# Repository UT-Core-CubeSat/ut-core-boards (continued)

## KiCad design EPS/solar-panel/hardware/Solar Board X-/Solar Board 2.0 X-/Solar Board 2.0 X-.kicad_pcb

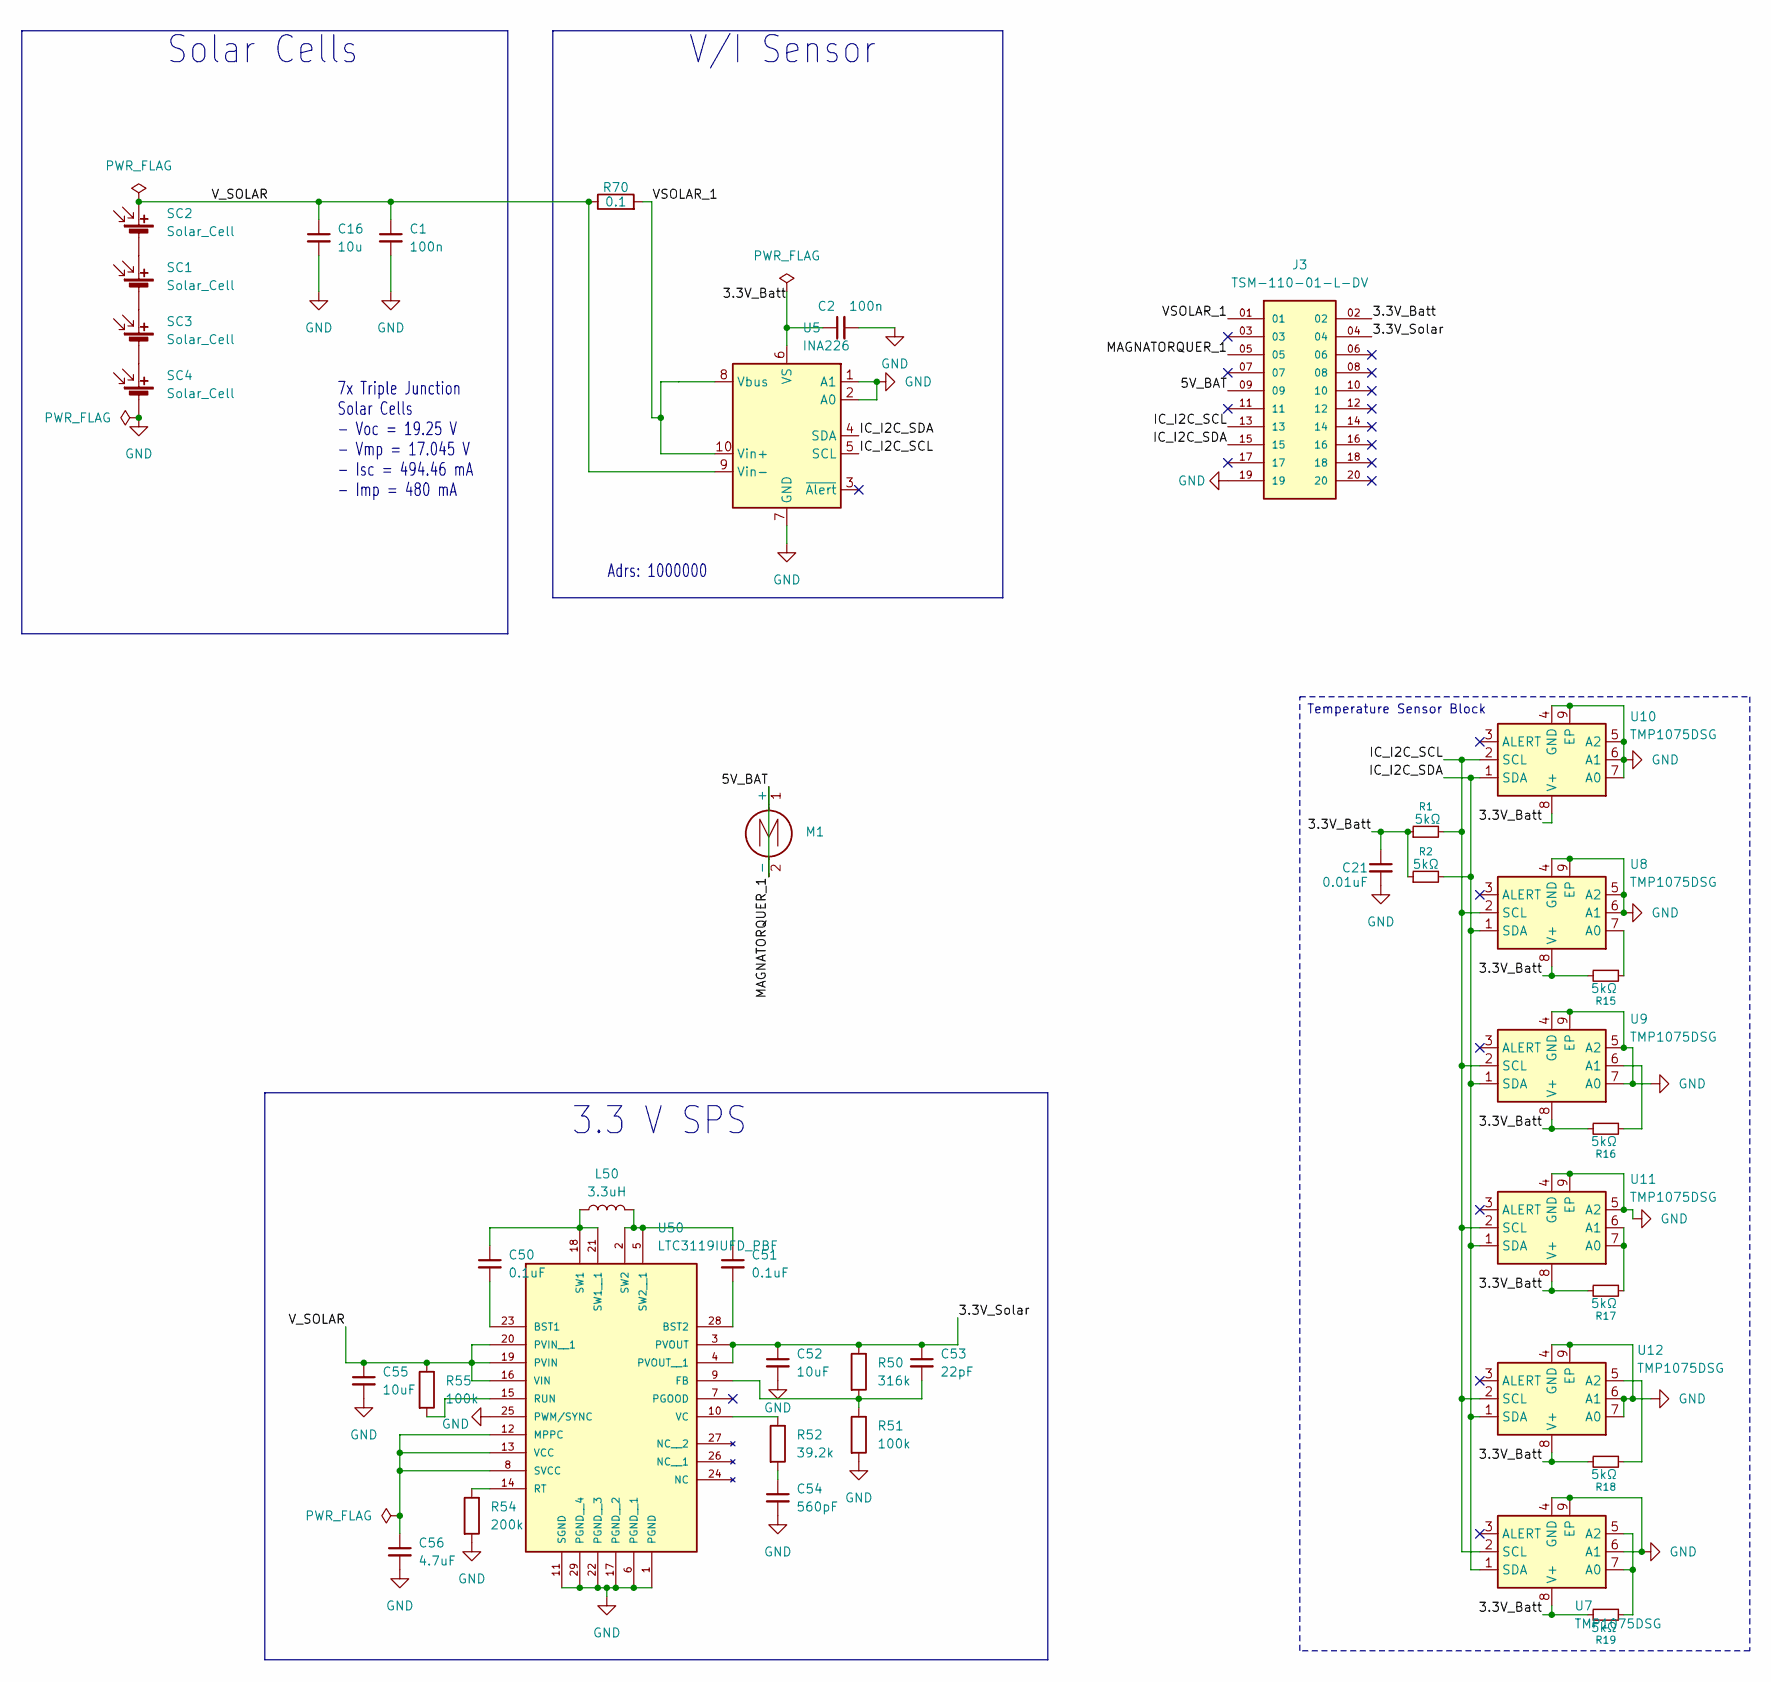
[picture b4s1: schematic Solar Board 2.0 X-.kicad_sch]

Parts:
C1, C2: 100n; C_0603_1608Metric
C16: 10u; C_0603_1608Metric
C21: 0.01uF; C_0402_1005Metric
C50, C51: 0.1uF; C_0201_0603Metric
C52: 10uF; C_0201_0603Metric
C53: 22pF; C_0201_0603Metric
C54: 560pF; C_0201_0603Metric
C55: 10uF; C_0603_1608Metric
C56: 4.7uF; C_0805_2012Metric
J3: TSM-110-01-L-DV; 2x10 Pin Header
L50: 3.3uH; L_0603_1608Metric
M1: Motor_DC; PinHeader_1x02_P2.54mm_Vertical
R1, R2, R15, R16, R17, R18, R19: 5kΩ; R_0201_0603Metric
R50: 316k; R_0201_0603Metric
R51, R55: 100k; R_0201_0603Metric
R52: 39.2k; R_0201_0603Metric
R54: 200k; R_0201_0603Metric
R70: 0.1; R_2512_6332Metric
SC1, SC2, SC3, SC4: Solar_Cell
U5: INA226; VSSOP-10_3x3mm_P0.5mm
U7, U8, U9, U10, U11, U12: TMP1075DSG; WSON-8-1EP_2x2mm_P0.5mm_EP0.9x1.6mm
U50: LTC3119IUFD_PBF; LTC3119

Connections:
/3.3V_Batt: C2.1, C21.1, J3.02, R1.1, R2.1, R15.2, R16.2, R17.2, R18.2, R19.2, U5.6 (VS), U7.8 (V+), U8.8 (V+), U9.8 (V+), U10.8 (V+), U11.8 (V+), U12.8 (V+)
/3.3V_Solar: C52.1, C53.1, J3.04, R50.1, U50.3 (PVOUT), U50.4 (PVOUT__1)
/5V_BAT: J3.05, J3.09, M1.1 (+), M1.2 (-)
/IC_I2C_SCL: J3.13, R1.2, U5.5 (SCL), U7.2 (SCL), U8.2 (SCL), U9.2 (SCL), U10.2 (SCL), U11.2 (SCL), U12.2 (SCL)
/IC_I2C_SDA: J3.15, R2.2, U5.4 (SDA), U7.1 (SDA), U8.1 (SDA), U9.1 (SDA), U10.1 (SDA), U11.1 (SDA), U12.1 (SDA)
/VSOLAR_1: J3.01, R70.2, U5.8 (Vbus), U5.10 (Vin+)
/V_SOLAR: C1.1, C16.1, C55.1, R55.1, R70.1, SC2.1 (+), U5.9 (Vin-), U50.16 (VIN), U50.19 (PVIN), U50.20 (PVIN__1)
GND: C1.2, C2.2, C16.2, C21.2, C52.2, C54.2, C55.2, C56.2, J3.19, R51.2, R54.2, SC4.2 (-), U5.1 (A1), U5.2 (A0), U5.7 (GND), U7.4 (GND), U7.6 (A1), U7.9 (EP), U8.4 (GND), U8.5 (A2), U8.6 (A1), U8.9 (EP), U9.4 (GND), U9.5 (A2), U9.7 (A0), U9.9 (EP), U10.4 (GND), U10.5 (A2), U10.6 (A1), U10.7 (A0), U10.9 (EP), U11.4 (GND), U11.5 (A2), U11.9 (EP), U12.4 (GND), U12.6 (A1), U12.7 (A0), U12.9 (EP), U50.1 (PGND), U50.6 (PGND__1), U50.11 (SGND), U50.17 (PGND__2), U50.22 (PGND__3), U50.25 (PWM/SYNC), U50.29 (PGND__4)
unnamed: C54.1, R52.2
unnamed: SC1.1 (+), SC2.2 (-)
unnamed: SC1.2 (-), SC3.1 (+)
unnamed: SC3.2 (-), SC4.1 (+)
unnamed: R19.1, U7.5 (A2), U7.7 (A0)
unnamed: R15.1, U8.7 (A0)
unnamed: R16.1, U9.6 (A1)
unnamed: R17.1, U11.6 (A1), U11.7 (A0)
unnamed: R18.1, U12.5 (A2)
unnamed: C50.2, U50.23 (BST1)
unnamed: C51.2, U50.28 (BST2)
unnamed: C53.2, R50.2, R51.1, U50.9 (FB)
unnamed: C56.1, U50.8 (SVCC), U50.12 (MPPC), U50.13 (VCC)
unnamed: R54.1, U50.14 (RT)
unnamed: R55.2, U50.15 (RUN)
unnamed: C50.1, L50.1, U50.18 (SW1), U50.21 (SW1__1)
unnamed: C51.1, L50.2, U50.2 (SW2), U50.5 (SW2__1)
unnamed: R52.1, U50.10 (VC)

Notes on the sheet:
V/I Sensor
Solar Cells
7x Triple Junction Solar Cells - Voc = 19.25 V - Vmp = 17.045 V - Isc = 494.46 mA - Imp = 480 mA
Adrs: 1000000
3.3 V SPS
Temperature Sensor Block

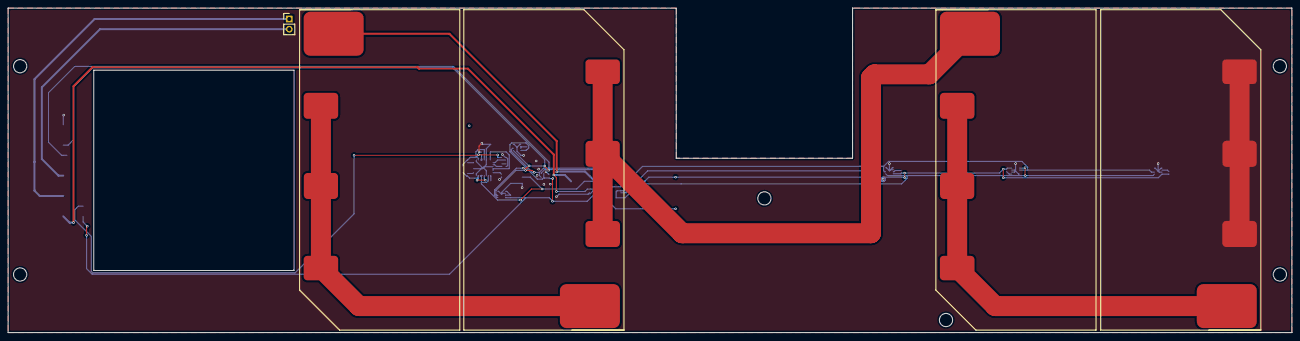
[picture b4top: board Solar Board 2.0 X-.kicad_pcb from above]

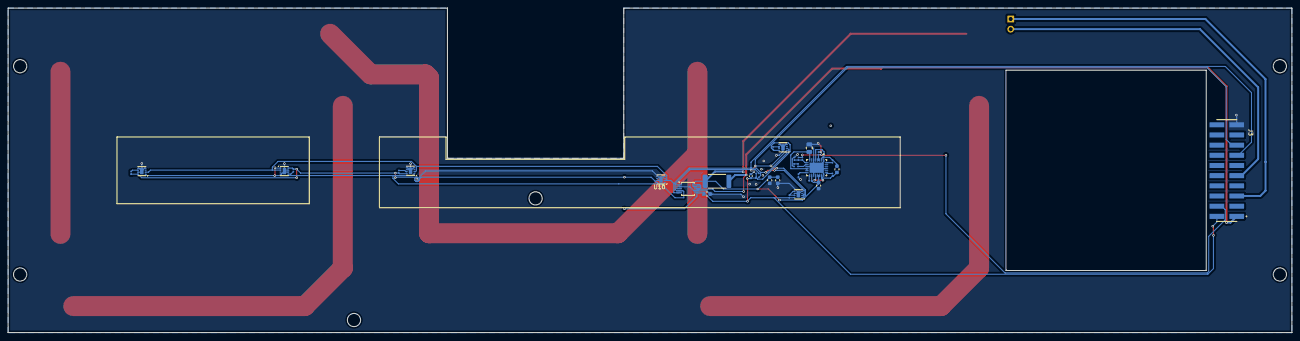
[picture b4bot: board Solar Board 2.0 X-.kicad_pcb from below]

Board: 4 copper layers, 320.5 x 81.0 mm, 39 parts (34 on the bottom side), 26 nets.

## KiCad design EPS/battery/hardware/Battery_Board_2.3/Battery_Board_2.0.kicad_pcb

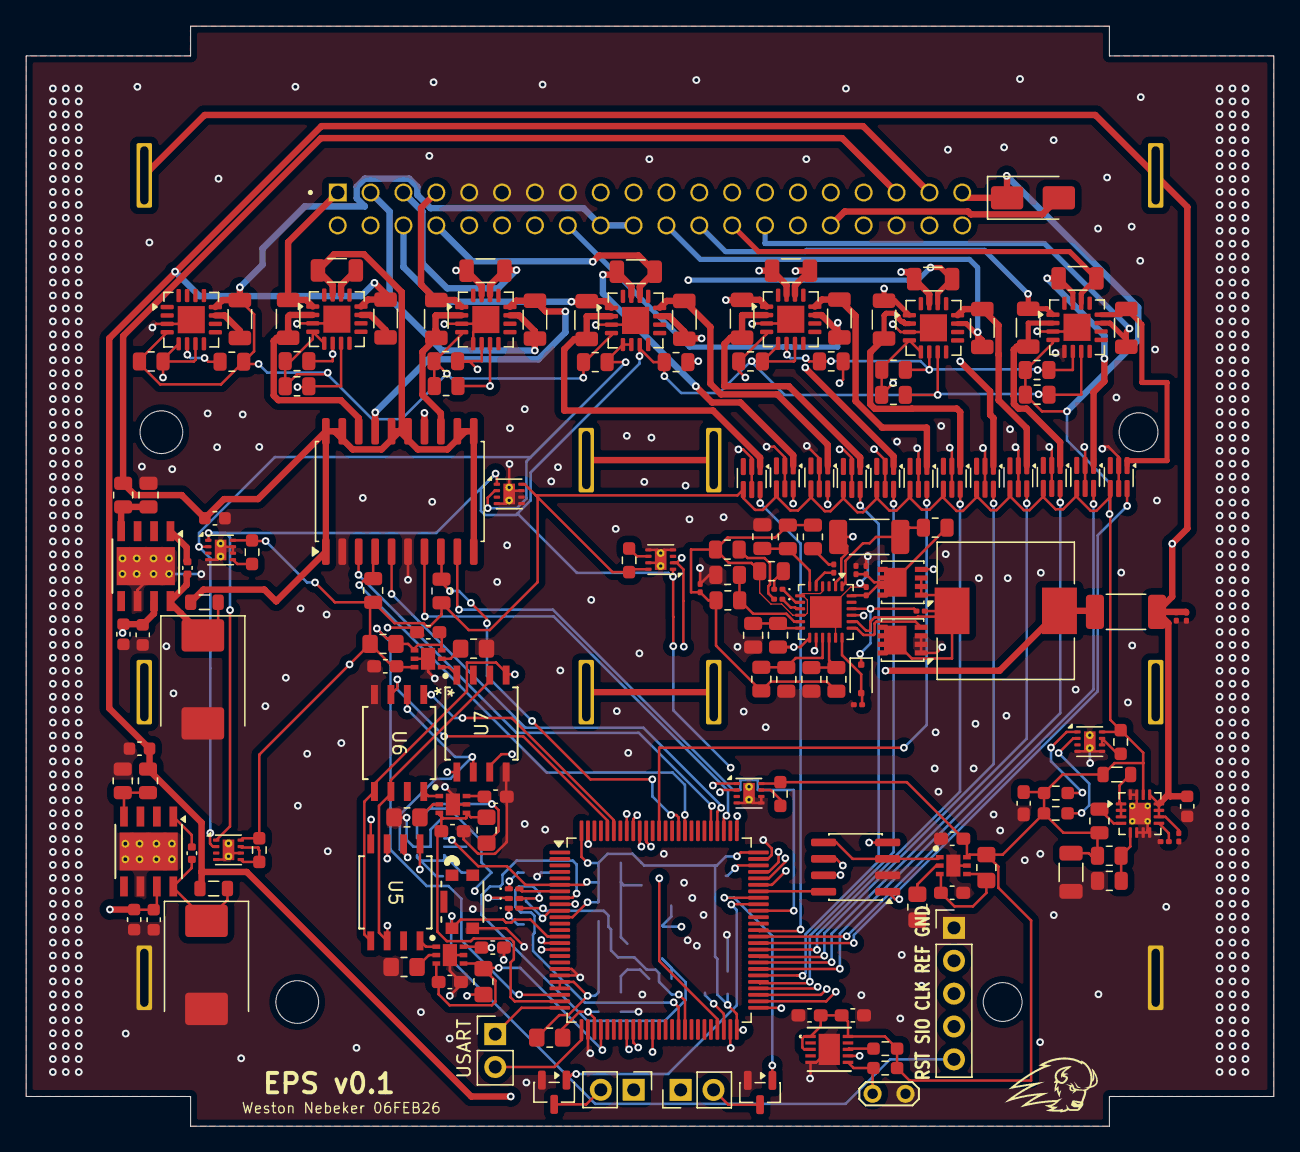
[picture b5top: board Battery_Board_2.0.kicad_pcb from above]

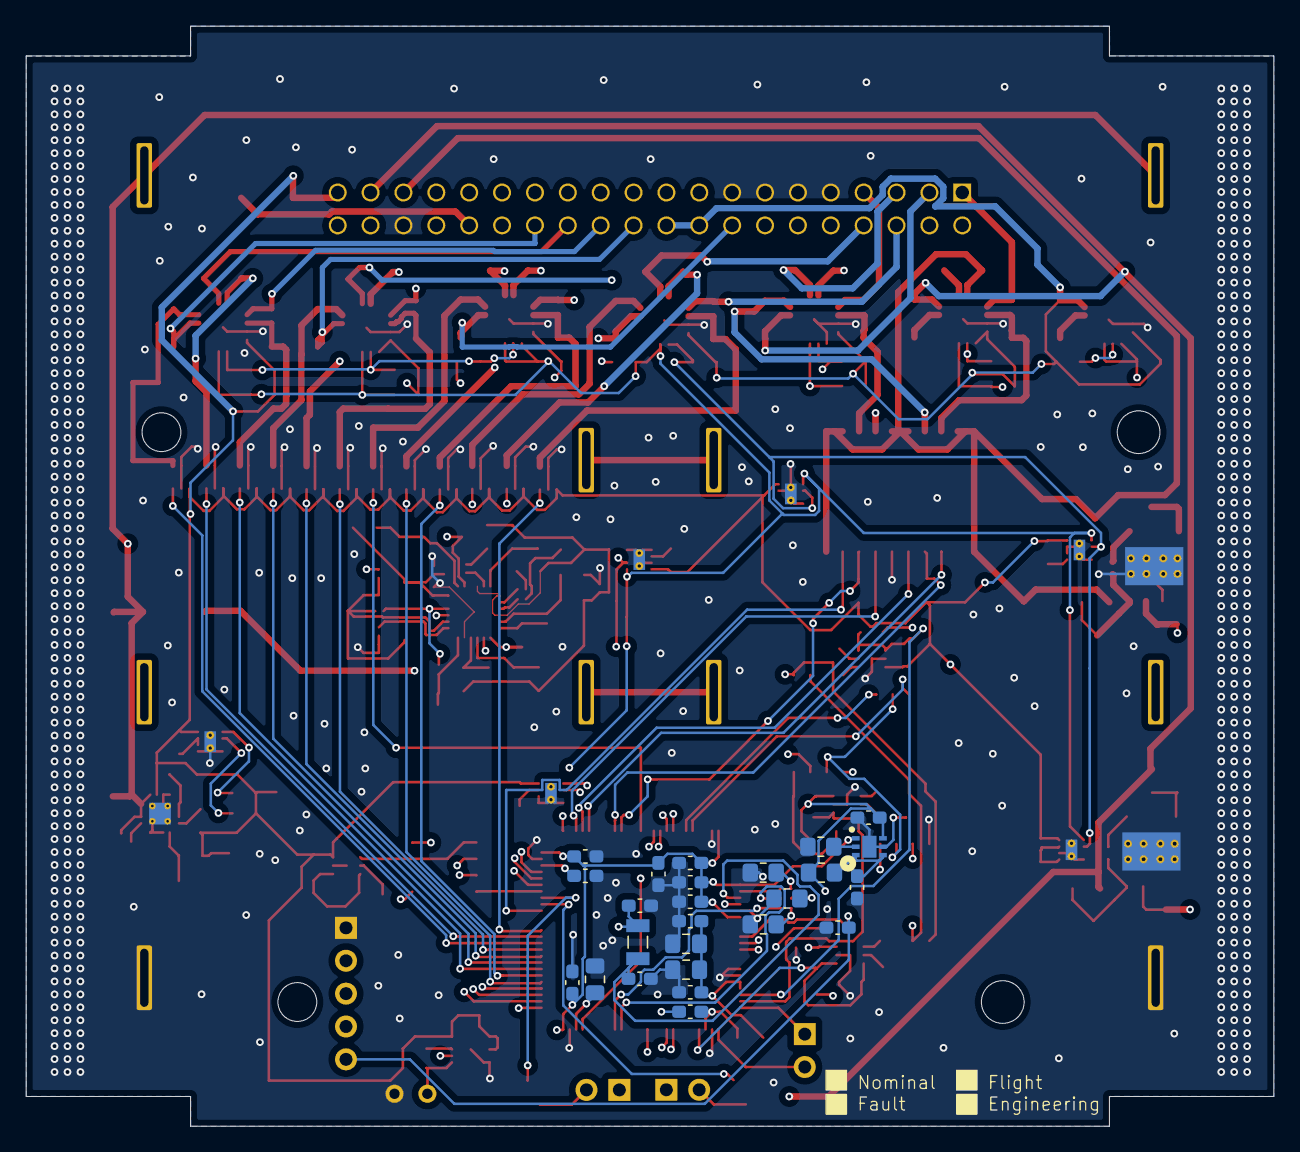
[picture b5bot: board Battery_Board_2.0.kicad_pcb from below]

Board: 4 copper layers, 96.4 x 85.0 mm, 205 parts (25 on the bottom side), 154 nets.

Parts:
BT1, BT2, BT5, BT6: Battery_Cell; 16340 Pin 1 Single
BT3, BT7: Battery_Cell; 16340 Battery
BT4, BT8: Battery_Cell; 16340 Pin 2 Single
C1, C1_RETRY1, C2_RETRY1, C3, C4, C5, C5_RETRY1, C6, C6_RETRY1, C7, C7_RETRY1, C9, C11, C21, C22, C25, C26, C29, C30, C31, C43, C144: 0.1uF; C_0603_1608Metric_Pad1.08x0.95mm_HandSolder
C2: 4.7uF; C_0805_2012Metric_Pad1.18x1.45mm_HandSolder
C8, C10: 12pF; C_0603_1608Metric_Pad1.08x0.95mm_HandSolder
C32: 1uF; C_0603_1608Metric_Pad1.08x0.95mm_HandSolder
C33: 10uF; C_0603_1608Metric_Pad1.08x0.95mm_HandSolder
C34: 0.1uF; C_0805_2012Metric_Pad1.18x1.45mm_HandSolder
C35: 1uF; C_0805_2012Metric_Pad1.18x1.45mm_HandSolder
C61, C63, C67, C90, C91, C94: 4.7uF; C_0603_1608Metric
C62: 10uF; C_0603_1608Metric
C64, C105: 0.1uF; C_0201_0603Metric
C65: 33nF; C_0201_0603Metric
C66, C92: 0.01uF; C_0402_1005Metric
C68: 22uF; C_1206_3216Metric
C80, C89, C991: 1uF; C_0201_0603Metric
C82, C83, C84, C85: 10uF; C_0201_0603Metric
D1, D5, D14: LED; LED_0201_0603Metric_Pad0.64x0.40mm_HandSolder
D6, D60: B340; D_SMC
D7: SS14; D_SMA
D50, D51, D52: LED; LED_0201_0603Metric
D53: BAT54J; D_SOD-323F
FB1: FerriteBead_Small; R_0805_2012Metric_Pad1.20x1.40mm_HandSolder
IC2, IC3, IC7, IC8, IC9: TPS2552DRVT-1
J2: IPS1-120-01-L-D-RA
J3: SWD; PinHeader_1x05_P2.54mm_Vertical
J4: USART; PinHeader_1x02_P2.54mm_Vertical
JP1: WD_Disable; TestPoint_2Pads_Pitch2.54mm_Drill0.8mm
L1: 2.2uH; L_0805_2012Metric
L2, L20: 22uH; L_0805_2012Metric
L25: 6.8uH; L_10.4x10.4_H4.8
Q100, Q101: SiS454DN; Vishay_PowerPAK_1212-8_Single
Q200, Q201: AO3400A; SOT-23
R1, R2, R12, R20, R34, R35, R40, R41, R45, R46, R52, R53: 0.33; R_1206_3216Metric
R1_FAULT1, R2_FAULT1, R5_FAULT1, R6_FAULT1, R7_FAULT1: 102kR; R_0805_2012Metric_Pad1.20x1.40mm_HandSolder
R1_ILIM1, R2_ILIM1: 88.7kR; R_0805_2012Metric_Pad1.20x1.40mm_HandSolder
R4, R21, R36, R39, R42, R47, R54: 0.05; R_1206_3216Metric
R5, R6, R22, R31, R32, R33, R37, R38, R43, R44, R48, R49, R50, R51, R58, R60, R64, R67, R80, R81, R83, R84, R85, R86, R87, R88: 10k; R_0805_2012Metric
R5_ILIM1, R6_ILIM1, R7_ILIM1: 226kR; R_0805_2012Metric_Pad1.20x1.40mm_HandSolder
R13, R14, R15, R16, R17, R18, R19: 5kR; R_0603_1608Metric_Pad0.98x0.95mm_HandSolder
R23: 100k; R_0805_2012Metric
R25: 25k; R_0805_2012Metric
R26, R27, R28: 470R; R_0805_2012Metric_Pad1.20x1.40mm_HandSolder
R55: 8k; R_0805_2012Metric
R57: 88.2k; R_0805_2012Metric
R59: 33k; R_0805_2012Metric
R65: 150k; R_0805_2012Metric
R66: 56k; R_0805_2012Metric
R82: 70k; R_0805_2012Metric
R91: 10K; R_0805_2012Metric
R128: 102k; R_0603_1608Metric_Pad0.98x0.95mm_HandSolder
R129: 16.5k; R_0603_1608Metric_Pad0.98x0.95mm_HandSolder
R300, R301: Heater; PinHeader_1x02_P2.54mm_Vertical
R570: 10.0k; R_0805_2012Metric
R571: 3.24k; R_0805_2012Metric
RSR1, RSR2: 0.01; R_2010_5025Metric_Pad1.40x2.65mm_HandSolder
SW1: KMR221GLFS; KMR221G LFS
U1, U2, U13, U23, U24, U25, U26, U27, U28, U29, U30, U31: MIC94090YC6; SOT-363_SC-70-6
U3: TCAN330; SOIC-8_3.9x4.9mm_P1.27mm
U4, U15, U17, U18, U32, U33, U34: INA3221; Texas_RGV0016A_VQFN-16-1EP_4x4mm_P0.65mm_EP2.1x2.1mm
U5, U6, U7: CY15B104QN-50SXI
U8, U9, U10, U11, U12, U14: TMP1075DSG; WSON-8-1EP_2x2mm_P0.5mm_EP0.9x1.6mm_ThermalVias
U16: STM32U5A5VJTx; LQFP-100_14x14mm_P0.5mm
U19: ITS716G; SOIC-20W_7.5x12.8mm_P1.27mm
U21, U221: TPS5430DDA; TI_SO-PowerPAD-8_ThermalVias
U22: TPS62130; VQFN-16-1EP_3x3mm_P0.5mm_EP1.68x1.68mm_ThermalVias
U50: BQ24610; VQFN-24-1EP_4x4mm_P0.5mm_EP2.45x2.45mm
U114: TPS3430WQDRCRQ1
Y1: ABS07AIG-32.768KHZ-9-1-T; ABS07AIG-32

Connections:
/3.3V_Batt: C9.1, C11.1, C21.1, C22.1, C25.1, C26.1, C43.1, C68.1, C144.2, D7.1 (K), IC2.6 (IN), IC3.6 (IN), IC7.6 (IN), IC8.6 (IN), IC9.6 (IN), J2.18, J2.20, J2.39, L1.2, R1_FAULT1.1, R2_FAULT1.2, R5.1, R5_FAULT1.2, R6.1, R6_FAULT1.2, R7_FAULT1.2, R13.1, R14.1, R15.2, R16.2, R17.2, R18.2, R19.2, R22.1, R23.1, R25.1, R31.1, R32.1, R33.1, R37.1, R38.1, R39.2, R43.1, R44.1, R48.1, R49.1, R50.1, R51.1, R80.2, R81.2, R128.2, R129.2, U1.4 (IN), U2.4 (IN), U4.4 (VS), U8.8 (V+), U9.8 (V+), U10.8 (V+), U11.8 (V+), U12.8 (V+), U13.4 (IN), U14.8 (V+), U15.4 (VS), U17.4 (VS), U18.4 (VS), U18.12 (IN+1), U22.14 (VOS), U23.4 (IN), U24.4 (IN), U25.4 (IN), U26.4 (IN), U27.4 (IN), U28.4 (IN), U29.4 (IN), U30.4 (IN), U31.4 (IN), U32.4 (VS), U32.5 (A0), U33.4 (VS), U33.5 (A0), U34.4 (VS), U114.1 (VDD1), U114.3 (SET0), U114.10 (VDD2)
/3.3V_Solar: D7.2 (A), J2.32
/5V_Batt: C94.1, J2.37, L20.2, R54.2, R300.1, R301.1, R570.1, U32.12 (IN+1)
/12V_Batt: C67.1, J2.35, L2.2, R47.2, R57.1, U19.1 (VBB), U19.10 (VBB), U19.11 (VBB), U19.12 (VBB), U19.15 (VBB), U19.16 (VBB), U19.19 (VBB), U19.20 (VBB), U32.15 (IN+2)
/ACN: R91.2, RSR2.1, U50.1 (ACN)
/ACP: J2.30, RSR2.2, U50.2 (ACP)
/ACSET: R59.1, R60.2, U50.16 (ACSET)
/BTST: C105.2, D53.1 (K), U50.22 (BTST)
/Battery: BT1.1 (+), BT5.1 (+), C61.1, C62.1, C63.1, C64.1, C84.2, C85.2, C90.1, C91.1, R82.2, RSR1.1, U21.7 (VIN), U22.10 (VIN), U22.11 (VIN), U22.12 (VIN), U22.13 (EN), U50.13 (SRN), U221.7 (VIN)
/HIDRV: Q100.4 (G), U50.21 (HIDRV)
/Heater1PWM: Q200.1 (G), U16.68 (PA9)
/Heater2PWM: Q201.1 (G), U16.67 (PA8)
/IC2_I2C_SCL: R5.2, R37.2, R43.2, U4.6 (SCL), U16.15 (PC0), U18.6 (SCL), U32.6 (SCL)
/IC2_I2C_SDA: R6.2, R38.2, R44.2, U4.7 (SDA), U16.16 (PC1), U18.5 (A0), U18.7 (SDA), U32.7 (SDA)
/IC_I2C_SCL: R13.2, R32.2, R33.2, R50.2, R51.2, U8.2 (SCL), U9.2 (SCL), U10.2 (SCL), U11.2 (SCL), U12.2 (SCL), U14.2 (SCL), U15.6 (SCL), U16.92 (PB6), U17.6 (SCL), U33.6 (SCL), U34.5 (A0), U34.6 (SCL)
/IC_I2C_SDA: R14.2, R22.2, R31.2, R48.2, R49.2, U8.1 (SDA), U9.1 (SDA), U10.1 (SDA), U11.1 (SDA), U12.1 (SDA), U14.1 (SDA), U15.7 (SDA), U16.93 (PB7), U17.5 (A0), U17.7 (SDA), U33.7 (SDA), U34.7 (SDA)
/ISET1: R66.1, R67.2, U50.11 (ISET1)
/ISET2: R64.2, R65.1, U50.15 (ISET2)
/LODRV: Q101.4 (G), U50.19 (LODRV)
/MCU_2_1_Input: J2.06, R53.2, U34.1 (IN-3)
/MCU_2_1_Input_1: U16.63 (PC6), U26.6 (EN)
/MCU_2_1_Output_1: R53.1, U26.1 (OUT), U34.2 (IN+3)
/MCU_2_2_Input_1: U16.34 (PC5), U31.6 (EN)
/MCU_2_2_Output: J2.08, R46.2, U34.14 (IN-2)
/MCU_2_2_Output_1: R46.1, U31.1 (OUT), U34.15 (IN+2)
/MCU_3_1_Input_1: U16.33 (PC4), U25.6 (EN)
/MCU_3_1_Output: J2.10, R41.2, U34.11 (IN-1)
/MCU_3_1_Output_1: R41.1, U25.1 (OUT), U34.12 (IN+1)
/MCU_3_2_Input_1: U16.56 (PD9), U24.6 (EN)
/MCU_3_2_Output: J2.12, R35.2, U17.1 (IN-3)
/MCU_3_2_Output_1: R35.1, U17.2 (IN+3), U24.1 (OUT)
/MCU_4_1_Input_1: U16.55 (PD8), U30.6 (EN)
/MCU_4_1_Output: J2.14, R20.2, U17.14 (IN-2)
/MCU_4_1_Output_1: R20.1, U17.15 (IN+2), U30.1 (OUT)
/MCU_4_2_Input_1: U16.88 (PD7), U27.6 (EN)
/MCU_4_2_Output: J2.16, R2.2, U17.11 (IN-1)
/MCU_4_2_Output_1: R2.1, U17.12 (IN+1), U27.1 (OUT)
/MCU_5_1_Input_1: U16.60 (PD13), U23.6 (EN)
/MCU_5_1_Output: J2.02, R52.2, U33.1 (IN-3)
/MCU_5_1_Output_1: R52.1, U23.1 (OUT), U33.2 (IN+3)
/MCU_5_2_Input_1: U16.59 (PD12), U29.6 (EN)
/MCU_5_2_Output: J2.04, R45.2, U33.14 (IN-2)
/MCU_5_2_Output_1: R45.1, U29.1 (OUT), U33.15 (IN+2)
/MCU_6_1_Input_1: U16.58 (PD11), U28.6 (EN)
/MCU_6_1_Output: J2.22, R40.2, U33.11 (IN-1)
/MCU_6_1_Output_1: R40.1, U28.1 (OUT), U33.12 (IN+1)
/MCU_6_2_Input_1: U2.6 (EN), U16.57 (PD10)
/MCU_6_2_Output: J2.24, R34.2, U15.1 (IN-3)
/MCU_6_2_Output_1: R34.1, U2.1 (OUT), U15.2 (IN+3)
/MCU_7_1_Input_1: U13.6 (EN), U16.62 (PD15)
/MCU_7_1_Output: J2.26, R12.2, U15.14 (IN-2)
/MCU_7_1_Output_1: R12.1, U13.1 (OUT), U15.15 (IN+2)
/MCU_7_2_Input_1: U1.6 (EN), U16.61 (PD14)
/MCU_7_2_Output: J2.28, R1.2, U15.11 (IN-1)
/MCU_7_2_Output_1: R1.1, U1.1 (OUT), U15.12 (IN+1)
/MCU_100_Pin/CANH: J2.40, U3.7 (CANH)
/MCU_100_Pin/CANL: J2.38, U3.6 (CANL)
/MCU_100_Pin/MCU1_CS1: U5.1 (*CS), U16.47 (PB10)
/MCU_100_Pin/MCU1_CS2: U6.1 (*CS), U16.95 (PB8)
/MCU_100_Pin/MCU1_CS3: U7.1 (*CS), U16.90 (PB4)
/MCU_100_Pin/MCU1_FRAM1_F: C5_RETRY1.1, IC7.3 (~FAULT), IC7.4 (EN), R5_FAULT1.1, U16.29 (PA4)
/MCU_100_Pin/MCU1_FRAM2_F: C6_RETRY1.1, IC8.3 (~FAULT), IC8.4 (EN), R6_FAULT1.1, U16.24 (PA1)
/MCU_100_Pin/MCU1_FRAM3_F: C7_RETRY1.1, IC9.3 (~FAULT), IC9.4 (EN), R7_FAULT1.1, U16.23 (PA0)
/MCU_100_Pin/MCU1_SPI2_MISO: U5.2 (SO), U6.2 (SO), U7.2 (SO), U16.53 (PB14)
/MCU_100_Pin/MCU1_SPI2_MOSI: U5.5 (SI), U6.5 (SI), U7.5 (SI), U16.54 (PB15)
/MCU_100_Pin/MCU1_SPI2_SCK: U5.6 (SCK), U6.6 (SCK), U7.6 (SCK), U16.52 (PB13)
/MCU_100_Pin/MCU1_WD: U16.37 (PB2), U114.7 (WDI)
/MCU_100_Pin/MCU1_WP1: U5.3 (*WP), U16.51 (PB12)
/MCU_100_Pin/MCU1_WP2: U6.3 (*WP), U16.96 (PB9)
/MCU_100_Pin/MCU1_WP3: U7.3 (*WP), U16.91 (PB5)
/MCU_100_Pin/NRST1: C7.2, J3.5, SW1.4, U16.14 (NRST)
/MCU_100_Pin/PA10_1: U3.8 (S), U16.69 (PA10)
/MCU_100_Pin/PA11_1: U3.4 (RXD), U16.70 (PA11)
/MCU_100_Pin/PA12_1: U3.1 (TXD), U16.71 (PA12)
/MCU_100_Pin/PA13_1: J3.4, U16.72 (PA13)
/MCU_100_Pin/PA14_1: J3.3, U16.76 (PA14)
/MCU_100_Pin/PC14_1: C8.2, U16.8 (PC14), Y1.1
/MCU_100_Pin/PC15_1: C10.2, U16.9 (PC15), Y1.2
/MCU_100_Pin/PE10_1: D5.2 (A), U16.41 (PE10)
/MCU_100_Pin/PE11_1: D1.2 (A), U16.42 (PE11)
/MCU_100_Pin/USART2_1: J4.1, U16.25 (PA2)
/MCU_100_Pin/USART2_2: J4.2, U16.26 (PA3)
/MCU_100_Pin/VREF1: C1.2, C3.2, C4.2, C5.2, C6.2, C29.2, C33.2, FB1.2, IC2.1 (OUT), J3.2, U16.6 (VBAT), U16.11 (VDD), U16.28 (VDD), U16.50 (VDD), U16.75 (VDD), U16.100 (VDD)
/Motor_1_Input_1: U16.80 (PC12), U19.3 (IN1)
/Motor_1_Output: J2.01, R42.1, U32.1 (IN-3)
/Motor_1_Output_1: R42.2, U19.18 (OUT1), U32.2 (IN+3)
/Motor_2_Input_1: U16.79 (PC11), U19.5 (IN2)
/Motor_2_Output: J2.03, R36.1, U4.11 (IN-1)
/Motor_2_Output_1: R36.2, U4.12 (IN+1), U19.17 (OUT2)
/Motor_3_Input_1: U16.78 (PC10), U19.7 (IN3)
/Motor_3_Output: J2.05, R21.1, U4.14 (IN-2)
/Motor_3_Output_1: R21.2, U4.15 (IN+2), U19.14 (OUT3)
/Motor_4_Input_1: U16.66 (PC9), U19.9 (IN4)
/Motor_4_Output: J2.07, R4.1, U4.1 (IN-3)
/Motor_4_Output_1: R4.2, U4.2 (IN+3), U19.13 (OUT4)
/PG: D52.1 (K), U50.8 (~PG)
/PH: C105.1, L25.1, Q100.1 (S), Q100.2 (S), Q100.3 (S), Q101.5 (D), U50.20 (PH)
/REGN: C89.2, D53.2 (A), U50.18 (REGN)
/SRP: L25.2, RSR1.2, U50.14 (SRP)
/ST1/2_Motor_1/2: R80.1, U16.84 (PD3), U19.4 (ST1/2)
/ST3/4_Motor_3/4: R81.1, U16.85 (PD4), U19.8 (ST3/4)
/STAT1: D50.1 (K), U50.5 (STAT1)
/STAT2: D51.1 (K), U50.9 (STAT2)
/TS: R84.1, R85.2, U50.6 (TS)
/TTC: C80.1, R59.2, R65.2, R66.2, R84.2, R86.1, R87.1, R88.1, U50.4 (CE), U50.7 (TTC), U50.10 (VREF)
/VFB: R82.1, R83.2, U50.12 (VFB)
GND: BT4.2 (-), BT8.2 (-), C1.1, C1_RETRY1.2, C2.2, C2_RETRY1.2, C3.1, C4.1, C5.1, C5_RETRY1.2, C6.1, C6_RETRY1.2, C7.1, C7_RETRY1.2, C8.1, C9.2, C10.1, C11.2, C21.2, C22.2, C25.2, C26.2, C29.1, C30.1, C31.1, C32.1, C33.1, C34.2, C35.2, C43.2, C61.2, C62.2, C63.2, C64.2, C65.1, C67.2, C68.2, C80.2, C82.1, C83.1, C84.1, C85.1, C89.1, C90.2, C91.2, C94.2, C144.1, C991.2, D6.2 (A), D60.2 (A), IC2.5 (GND), IC2.7 (EP), IC3.5 (GND), IC3.7 (EP), IC7.5 (GND), IC7.7 (EP), IC8.5 (GND), IC8.7 (EP), IC9.5 (GND), IC9.7 (EP), J2.09, J2.11, J2.13, J2.15, J2.36, J3.1, JP1.2 (B), Q101.1 (S), Q101.2 (S), Q101.3 (S), Q200.2 (S), Q201.2 (S), R1_ILIM1.2, R2_ILIM1.2, R5_ILIM1.2, R6_ILIM1.2, R7_ILIM1.2, R26.2, R27.2, R28.2, R55.2, R58.2, R60.1, R64.1, R67.1, R83.1, R85.1, R571.2, SW1.3, U1.2 (GND), U1.5 (GND), U2.2 (GND), U2.5 (GND), U3.2 (GND), U4.3 (GND), U4.5 (A0), U4.17 (EP), U5.4 (VSS), U6.4 (VSS), U7.4 (VSS), U8.4 (GND), U8.5 (A2), U8.6 (A1), U8.9 (EP), U9.4 (GND), U9.5 (A2), U9.7 (A0), U9.9 (EP), U10.4 (GND), U10.5 (A2), U10.6 (A1), U10.7 (A0), U10.9 (EP), U11.4 (GND), U11.5 (A2), U11.9 (EP), U12.4 (GND), U12.6 (A1), U12.7 (A0), U12.9 (EP), U13.2 (GND), U13.5 (GND), U14.4 (GND), U14.6 (A1), U14.9 (EP), U15.3 (GND), U15.5 (A0), U15.17 (EP), U16.10 (VSS), U16.19 (VSSA), U16.20 (VREF-), U16.27 (VSS), U16.49 (VSS), U16.74 (VSS), U16.99 (VSS), U17.3 (GND), U17.17 (EP), U18.3 (GND), U18.17 (EP), U19.2 (GND1/2), U19.6 (GND3/4), U21.6 (GND), U21.9 (GNDPAD), U22.6 (GND), U22.7 (FSW), U22.8 (DEF), U22.15 (GND), U22.16 (GND), U22.17 (GND), U23.2 (GND), U23.5 (GND), U24.2 (GND), U24.5 (GND), U25.2 (GND), U25.5 (GND), U26.2 (GND), U26.5 (GND), U27.2 (GND), U27.5 (GND), U28.2 (GND), U28.5 (GND), U29.2 (GND), U29.5 (GND), U30.2 (GND), U30.5 (GND), U31.2 (GND), U31.5 (GND), U32.3 (GND), U32.17 (EP), U33.3 (GND), U33.17 (EP), U34.3 (GND), U34.17 (EP), U50.17 (GND), U50.25 (GND), U114.5 (GND), U114.11 (EPAD), U221.6 (GND), U221.9 (GNDPAD)
unnamed: BT2.1 (+), BT6.1 (+)
unnamed: BT3.1 (+), BT7.1 (+)
unnamed: BT3.2 (-), BT7.2 (-)
unnamed: D1.1 (K), R26.1
unnamed: D5.1 (K), R27.1
unnamed: C66.2, D6.1 (K), L2.1, U21.8 (PH)
unnamed: D14.2 (A), U16.7 (PC13)
unnamed: D14.1 (K), R28.1
unnamed: D50.2 (A), R86.2
unnamed: D51.2 (A), R87.2
unnamed: D52.2 (A), R88.2
unnamed: C92.2, D60.1 (K), L20.1, U221.8 (PH)
unnamed: C1_RETRY1.1, IC2.3 (~FAULT), IC2.4 (EN), R1_FAULT1.2
unnamed: IC2.2 (ILIM), R1_ILIM1.1
unnamed: C2_RETRY1.1, IC3.3 (~FAULT), IC3.4 (EN), R2_FAULT1.1
unnamed: IC3.2 (ILIM), R2_ILIM1.1
unnamed: IC3.1 (OUT), U3.3 (VCC), U3.5 (SHDN)
unnamed: IC7.2 (ILIM), R5_ILIM1.1
unnamed: IC7.1 (OUT), U5.8 (VDD)
unnamed: IC8.2 (ILIM), R6_ILIM1.1
unnamed: IC8.1 (OUT), U6.8 (VDD)
unnamed: IC9.2 (ILIM), R7_ILIM1.1
unnamed: IC9.1 (OUT), U7.8 (VDD)
unnamed: JP1.1 (A), R128.1, U114.6 (SET1)
unnamed: L1.1, U22.1 (SW), U22.2 (SW), U22.3 (SW)
unnamed: C82.2, C83.2, C991.1, Q100.5 (D), R91.1, U50.24 (VCC)
unnamed: Q200.3 (D), R301.2
unnamed: Q201.3 (D), R300.2
unnamed: R15.1, U8.7 (A0)
unnamed: R16.1, U9.6 (A1)
unnamed: R17.1, U11.6 (A1), U11.7 (A0)
unnamed: R18.1, U12.5 (A2)
unnamed: R19.1, U14.5 (A2), U14.7 (A0)
unnamed: C2.1, U16.48 (VCAP)
unnamed: C31.2, C32.2, C34.1, C35.1, FB1.1, U16.21 (VREF+), U16.22 (VDDA)
unnamed: C30.2, U16.73 (VDDUSB)
unnamed: R39.1, U18.11 (IN-1)
unnamed: C66.1, U21.1 (BOOT)
unnamed: R57.2, R58.1, U21.4 (VSENSE)
unnamed: R25.2, R55.1, U22.5 (FB)
unnamed: R23.2, U22.4 (PG)
unnamed: C65.2, U22.9 (SS/TR)
unnamed: R54.1, U32.11 (IN-1)
unnamed: R47.1, U32.14 (IN-2)
unnamed: R129.1, U114.8 (*WDO)
unnamed: C92.1, U221.1 (BOOT)
unnamed: R570.2, R571.1, U221.4 (VSENSE)
